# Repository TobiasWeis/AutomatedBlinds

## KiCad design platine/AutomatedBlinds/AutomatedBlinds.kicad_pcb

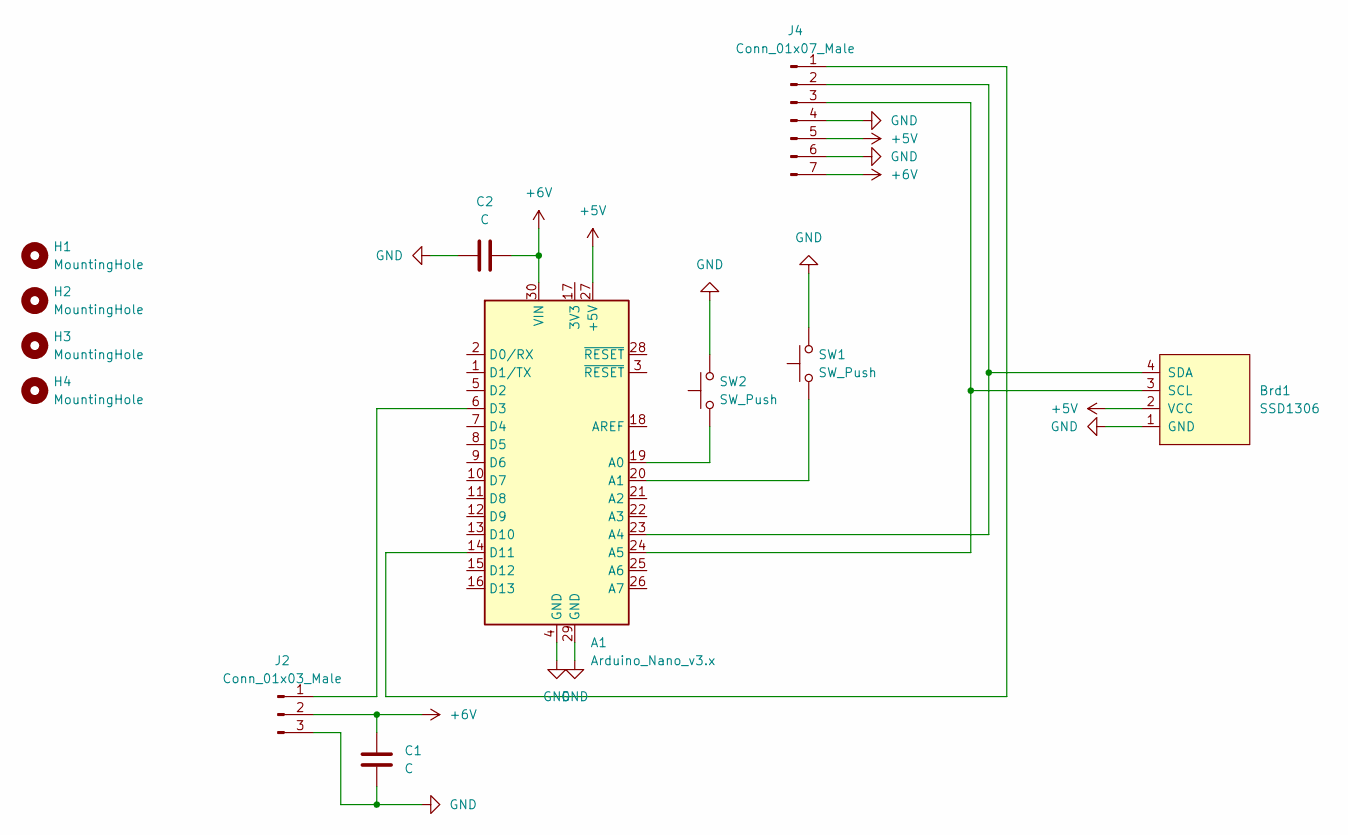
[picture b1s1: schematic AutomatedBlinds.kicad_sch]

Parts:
A1: Arduino_Nano_v3.x; Arduino_Nano
Brd1: SSD1306; 128x64OLED
C1, C2: C; CP_Radial_D10.0mm_P2.50mm
H1, H2, H3, H4: MountingHole; MountingHole_2.2mm_M2
J2: Conn_01x03_Male; PinHeader_1x03_P2.54mm_Vertical
J4: Conn_01x07_Male; PinHeader_1x07_P2.54mm_Vertical
SW1, SW2: SW_Push; SW_PUSH_6mm_H4.3mm

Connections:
+5V: A1.27 (+5V), Brd1.2 (VCC), J4.5
+6V: A1.30 (VIN), C1.1, C2.1, J2.2, J4.7
GND: A1.4 (GND), A1.29 (GND), Brd1.1 (GND), C1.2, C2.2, J2.3, J4.4, J4.6, SW1.2, SW2.2
unnamed: A1.19 (A0), SW2.1
unnamed: A1.20 (A1), SW1.1
unnamed: A1.23 (A4), Brd1.4 (SDA), J4.2
unnamed: A1.24 (A5), Brd1.3 (SCL), J4.3
unnamed: A1.6 (D3), J2.1
unnamed: A1.14 (D11), J4.1

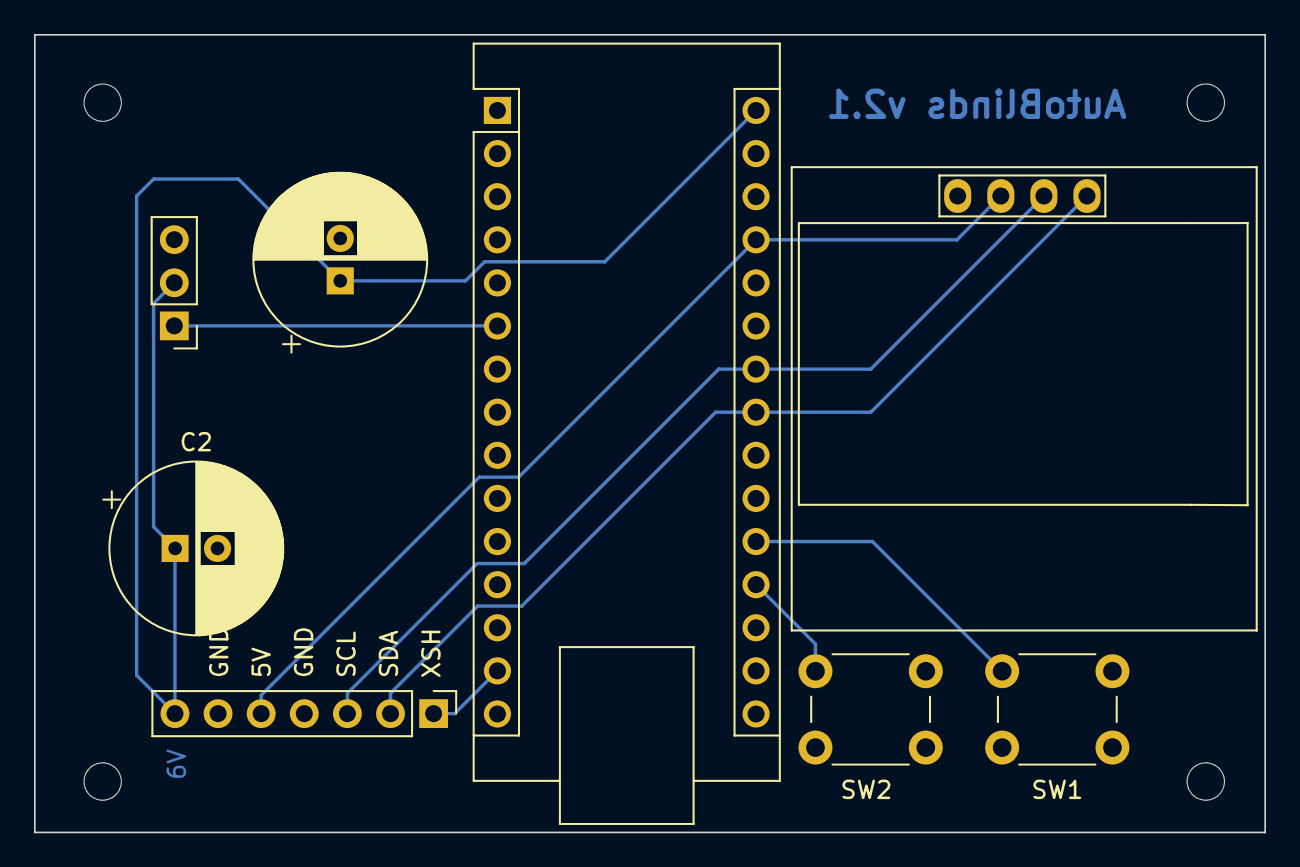
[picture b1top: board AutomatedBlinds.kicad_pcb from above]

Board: 2 copper layers, 72.5 x 47.0 mm, 12 parts (0 on the bottom side), 9 nets.

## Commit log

2021-10-24 initial commit of arduino code
2021-10-26 added 3d mounting files
2021-10-29 code works with TOF sensors
2021-11-06 added adapter and tof-sensor-3d-file
2021-11-07 added tof-mount scad file
2025-11-12 minor
2025-11-12 added kicad files
